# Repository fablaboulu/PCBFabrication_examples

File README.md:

# PCBFabrication Examples
We have added all the necessary files to design and fabricate a circuit in Fab Lab Oulu using SMD component. The repository includes:

* A PDF file including a design tutorial
* The design files to create two different boards:
  * A simple design with a button and a LED (Design 1). You can find the tinkercad simulation [here](https://www.tinkercad.com/things/7kGoBq8Yi5c).
  * A simple design to control a RGB LED using arduino (Design 2). You can find the tinkercad simulation [here](https://www.tinkercad.com/things/i23wB4gbnYI).

## Additional material
* [A video](https://youtu.be/-7NV_vIO7Lk) with some instructions on setting up the SRM-2+
* [A Tutorial on PCB fabrication](https://wiki.oulu.fi/display/FLOWS/Milling)

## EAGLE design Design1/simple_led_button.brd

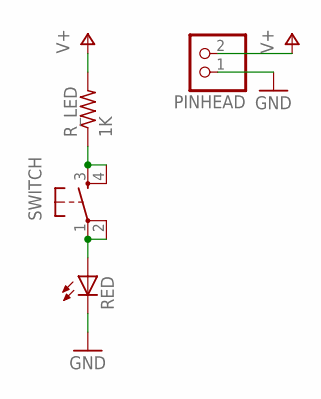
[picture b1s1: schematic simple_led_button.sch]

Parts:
PINHEAD: PINHD-1X2; 1X02
RED: LEDFAB1206; LED1206FAB
R_LED: 1K; R1206FAB
SWITCH: 6MM_SWITCH6MM_SWITCH; 6MM_SWITCH

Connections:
GND: PINHEAD.1, RED.2 (C)
unnamed: R_LED.1, SWITCH.3 (S), SWITCH.4 (S1)
unnamed: RED.1 (A), SWITCH.1, SWITCH.2 (P1)
V+: PINHEAD.2, R_LED.2

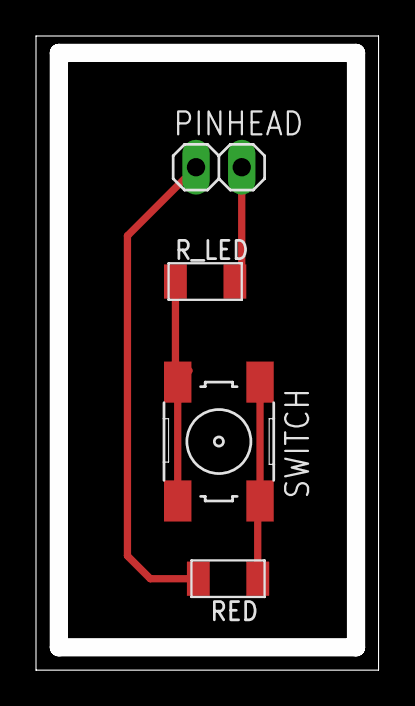
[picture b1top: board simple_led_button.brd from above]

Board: 2 copper layers, 18.0 x 34.2 mm, 4 parts (0 on the bottom side), 4 nets.

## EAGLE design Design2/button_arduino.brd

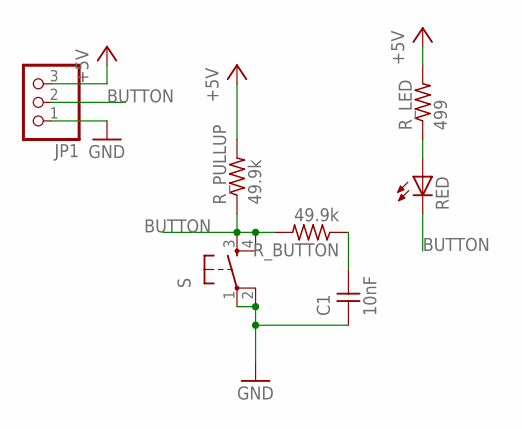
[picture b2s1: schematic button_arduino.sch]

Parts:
C1: 10nF; C1206FAB
JP1: PINHD-1X3; 1X03
RED: LEDFAB1206; LED1206FAB
R_BUTTON: 49.9k; R1206FAB
R_LED: 499; R1206FAB
R_PULLUP: 49.9k; R1206FAB
S: 6MM_SWITCH6MM_SWITCH; 6MM_SWITCH

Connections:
+5V: JP1.3, R_LED.2, R_PULLUP.2
BUTTON: JP1.2, RED.2 (C), R_BUTTON.2, R_PULLUP.1, S.3 (S), S.4 (S1)
GND: C1.1, JP1.1, S.1, S.2 (P1)
unnamed: RED.1 (A), R_LED.1
unnamed: C1.2, R_BUTTON.1

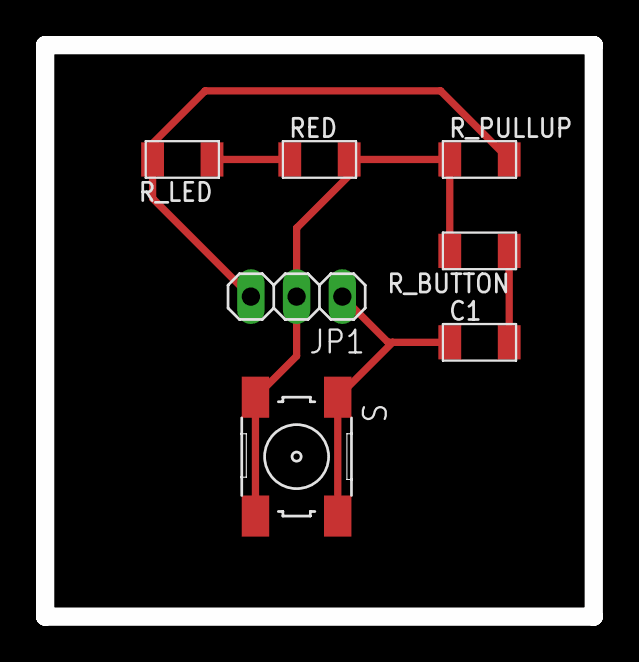
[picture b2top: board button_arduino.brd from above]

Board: 2 copper layers, 30.5 x 31.8 mm, 7 parts (0 on the bottom side), 5 nets.

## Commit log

2020-02-10 Added traces
